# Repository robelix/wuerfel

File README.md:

wuerfel
=======

Elektronischer Würfel - Lötworkshop für Anfänger

Schaltung und Layout von elektronischem Würfel. 
Originalschaltung von http://www.lte.lu/wiki/Elektronischer_W%C3%BCrfel_/_D%C3%A9_%C3%A9lectronique mit einer Modifikation: die mittlere LED wird nun über einen als Inverter benutzten Nand gegen Ground angesteuert. Ansonsten konnte es passieren, daß die manchmal schwach leuchtet wenn sie das gar nicht sollte.

Der Lötworkshop findet am 19.1.2013 in Innsbruck statt
https://catbull.com/wiki/index.php/Elektronischer_W%C3%BCrfel

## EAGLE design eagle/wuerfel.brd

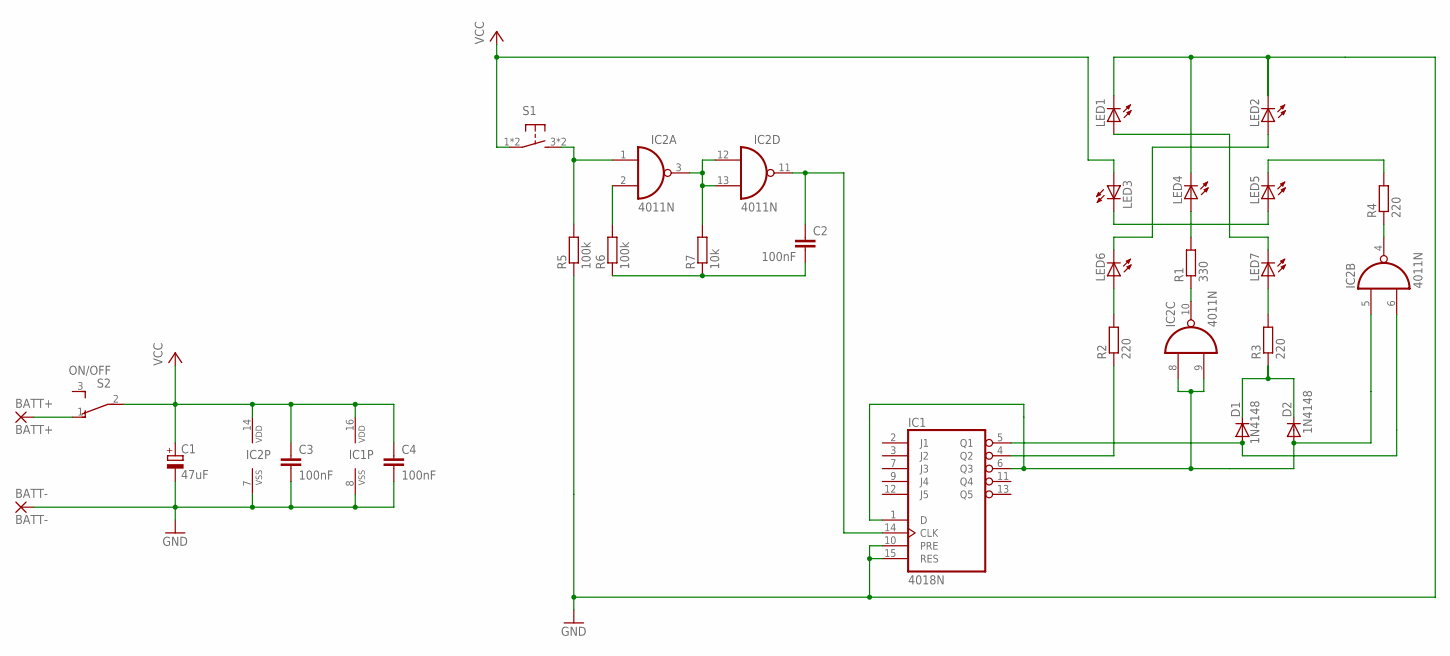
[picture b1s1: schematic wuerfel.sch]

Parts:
BATT+: BATT+; 2,54/0,8
BATT-: BATT-; 2,54/0,8
C1: 47uF; E2,5-5-L-12
C2, C3, C4: 100nF; C025-025X050
D1, D2: 1N4148; DO35-10
IC1: 4018N; DIL16
IC2: 4011N; DIL14
LED1, LED2, LED3, LED4, LED5, LED6, LED7: LED5MM
R1: 330; 0207/10
R2, R3, R4: 220; 0207/10
R5, R6: 100k; 0207/10
R7: 10k; 0207/10
S1: TASTER8MM; TASTER6X6
S2: ON/OFF; T215LB

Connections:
GND: BATT-.1, C1.-, C3.2, C4.2, IC1.8 (VSS), IC1.10 (PRE), IC1.15 (RES), IC2.7 (VSS), LED1.K (C), LED2.K (C), LED4.K (C), R5.1
unnamed: IC2.3 (O), IC2.12 (I0), IC2.13 (I1), R7.2
unnamed: IC2.2 (I1), R6.2
unnamed: BATT+.1, S2.1 (O)
unnamed: LED6.A, R2.2
unnamed: IC2.1 (I0), R5.2, S1.3, S1.4 (3)
unnamed: LED3.K (C), LED5.A
unnamed: LED2.A, LED6.K (C)
unnamed: LED1.A, LED7.K (C)
unnamed: C2.1, IC1.14 (CLK), IC2.11 (O)
unnamed: LED5.K (C), R4.2
unnamed: IC2.4 (O), R4.1
unnamed: LED4.A, R1.2
unnamed: LED7.A, R3.2
unnamed: D1.A, IC1.5 (Q1), IC2.6 (I1)
unnamed: D1.C, D2.C, R3.1
unnamed: IC1.4 (Q2), R2.1
unnamed: IC2.10 (O), R1.1
unnamed: D2.A, IC1.1 (D), IC1.6 (Q3), IC2.5 (I0), IC2.8 (I0), IC2.9 (I1)
unnamed: C2.2, R6.1, R7.1
VCC: C1.+, C3.1, C4.1, IC1.16 (VDD), IC2.14 (VDD), LED3.A, S1.1, S1.2 (1), S2.2

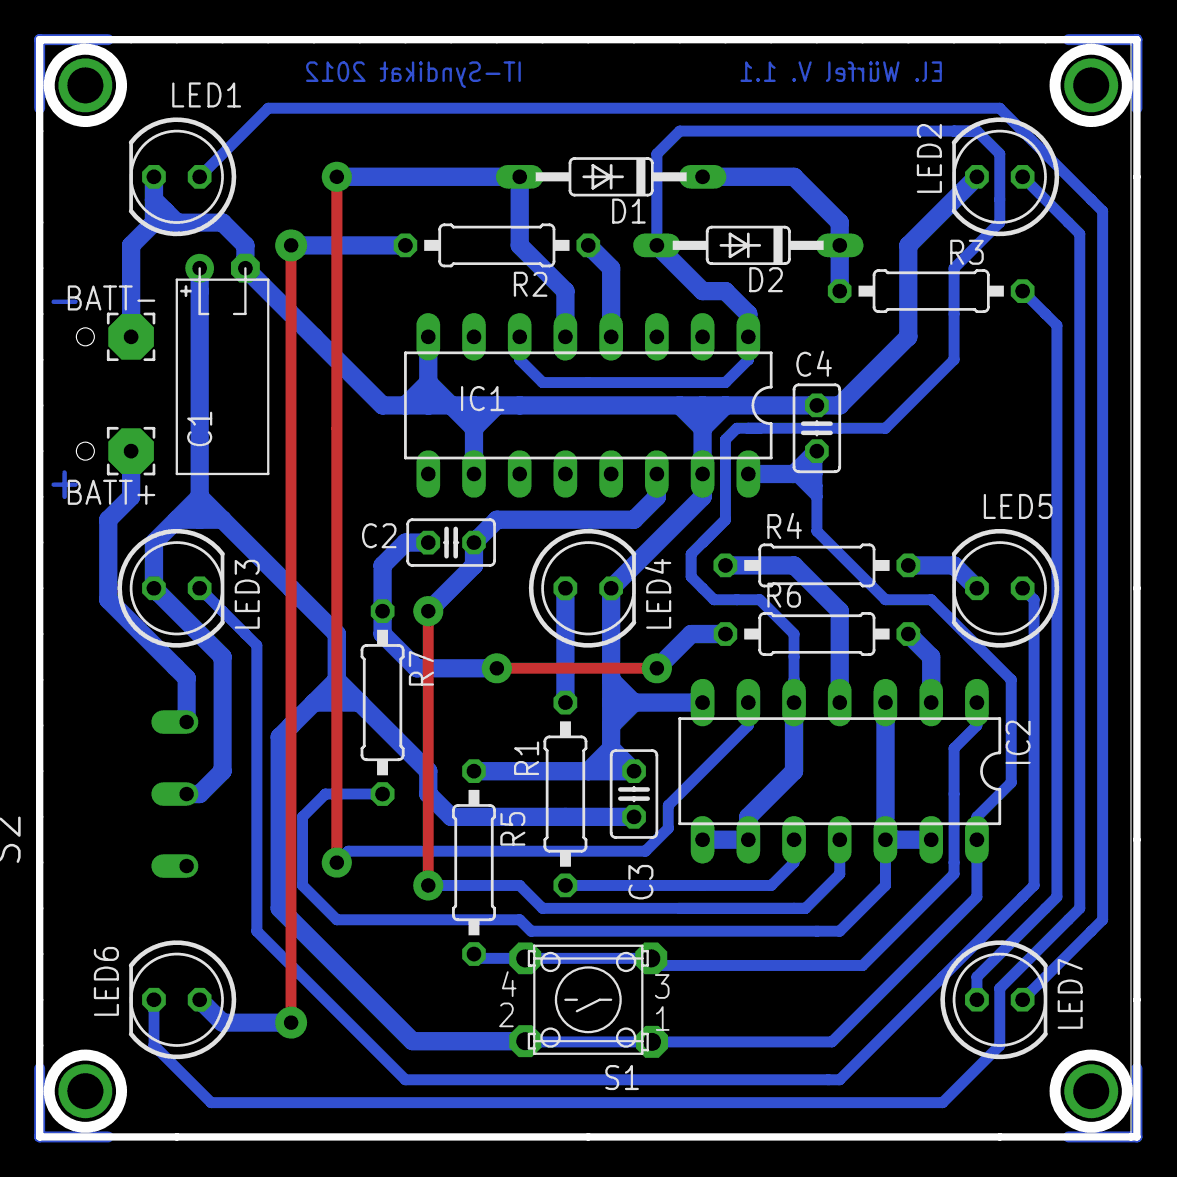
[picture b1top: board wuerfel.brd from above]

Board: 2 copper layers, 61.0 x 61.0 mm, 26 parts (1 on the bottom side), 21 nets.

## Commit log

2012-12-02 Wuerfel Schaltung und Layout
2013-07-17 bestückungsplan pdf
